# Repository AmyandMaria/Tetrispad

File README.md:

# TETRISPAD

This is a 4 key macropad with an OLED and a knob that I want to use for Tetris on TETR.IO. I play Tetris a lot on my computer, but I wanted a macropad to possibly improve playing performance. 

## CAD MODEL

## PCB

## SCHEMATIC

## FIRMWARE
I used KMK.

## BILL OF MATERIALS
- 4x Cherry MX Switches
- 4x Keycaps
- 4x M3x5x4 Heatset Inserts
- 4x M3x16mm SHCS Bolts
- 1x 0.91" 128x32 OLED Display
- 1x EC11 Rotary Encoder
- 1x XIAO RP2040
- 1x Case (3 printed parts)

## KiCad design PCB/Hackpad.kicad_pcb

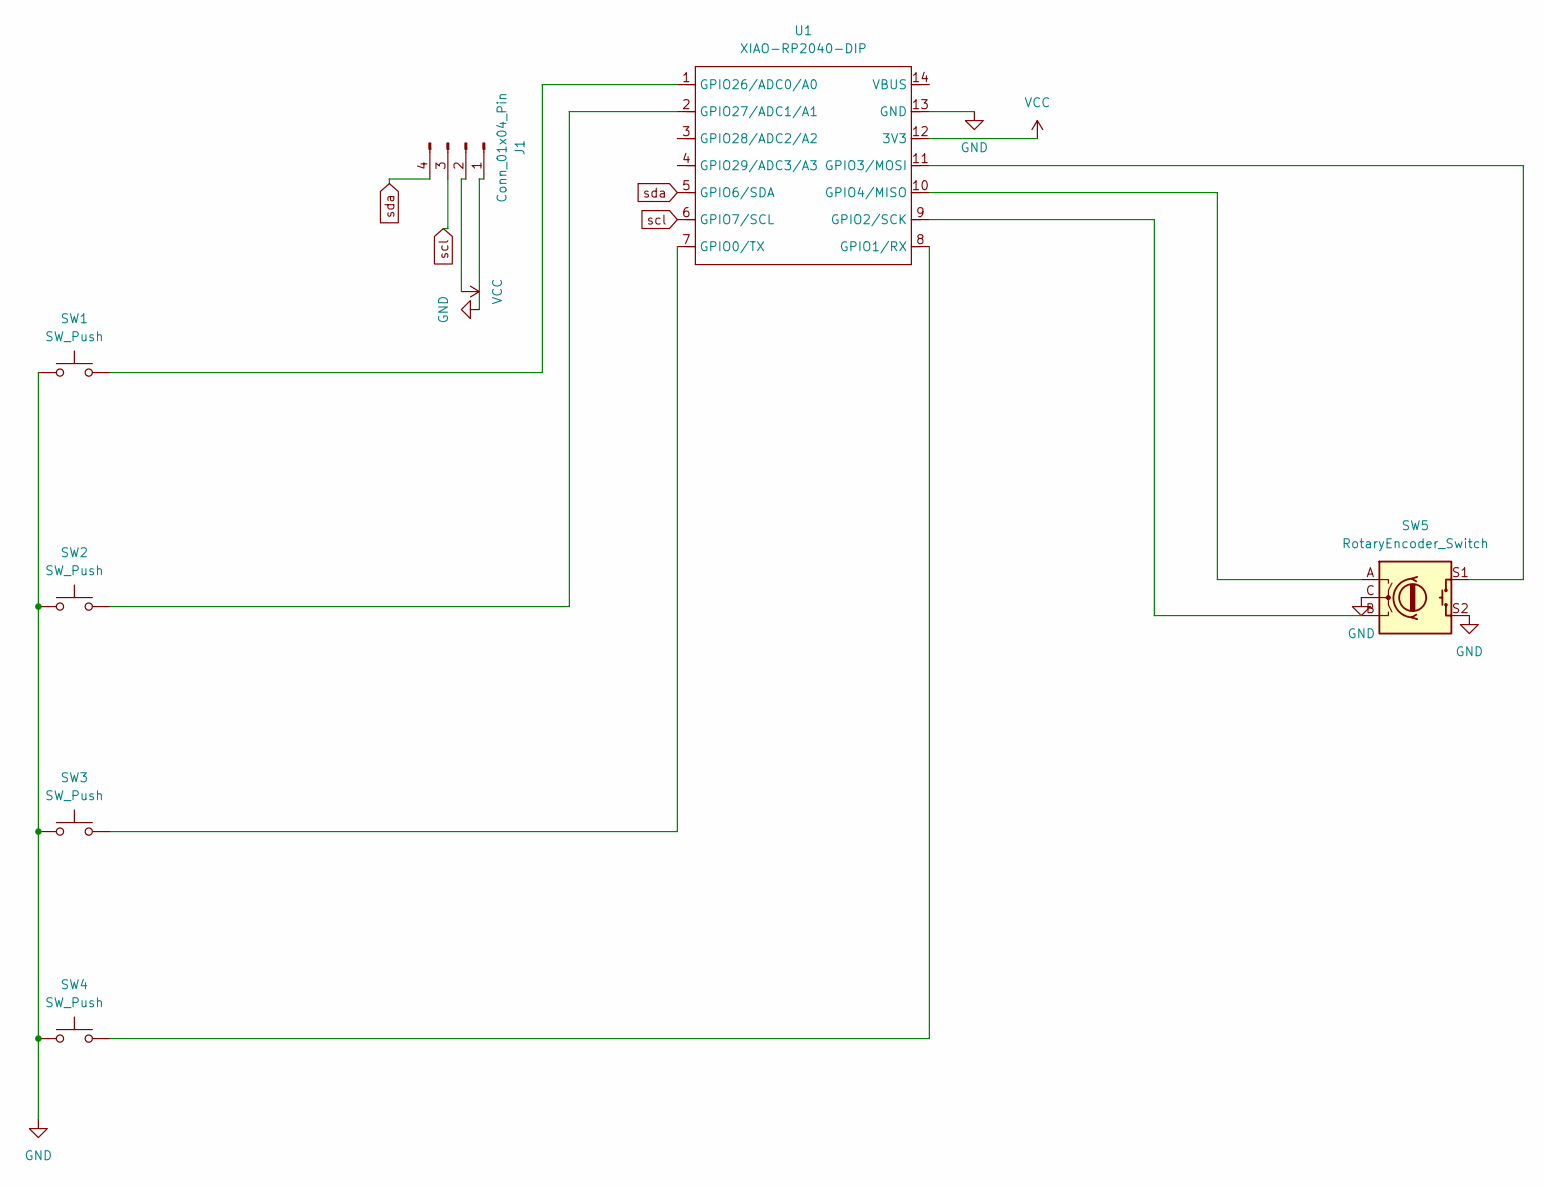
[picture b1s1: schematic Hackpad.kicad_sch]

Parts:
J1: Conn_01x04_Pin; SSD1306-0.91-OLED-4pin-128x32
SW1, SW2, SW3, SW4: SW_Push; SW_Cherry_MX_1.00u_PCB
SW5: RotaryEncoder_Switch; RotaryEncoder_Alps_EC11E-Switch_Vertical_H20mm
U1: XIAO-RP2040-DIP

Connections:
GND: J1.1, SW1.1, SW2.1, SW3.1, SW4.1, SW5.C, SW5.S2, U1.13 (GND)
unnamed: SW3.2, U1.7 (GPIO0/TX)
unnamed: SW4.2, U1.8 (GPIO1/RX)
unnamed: SW5.B, U1.9 (GPIO2/SCK)
unnamed: SW5.S1, U1.11 (GPIO3/MOSI)
unnamed: SW5.A, U1.10 (GPIO4/MISO)
unnamed: SW1.2, U1.1 (GPIO26/ADC0/A0)
unnamed: SW2.2, U1.2 (GPIO27/ADC1/A1)
VCC: J1.2, U1.12 (3V3)
scl: J1.3, U1.6 (GPIO7/SCL)
sda: J1.4, U1.5 (GPIO6/SDA)

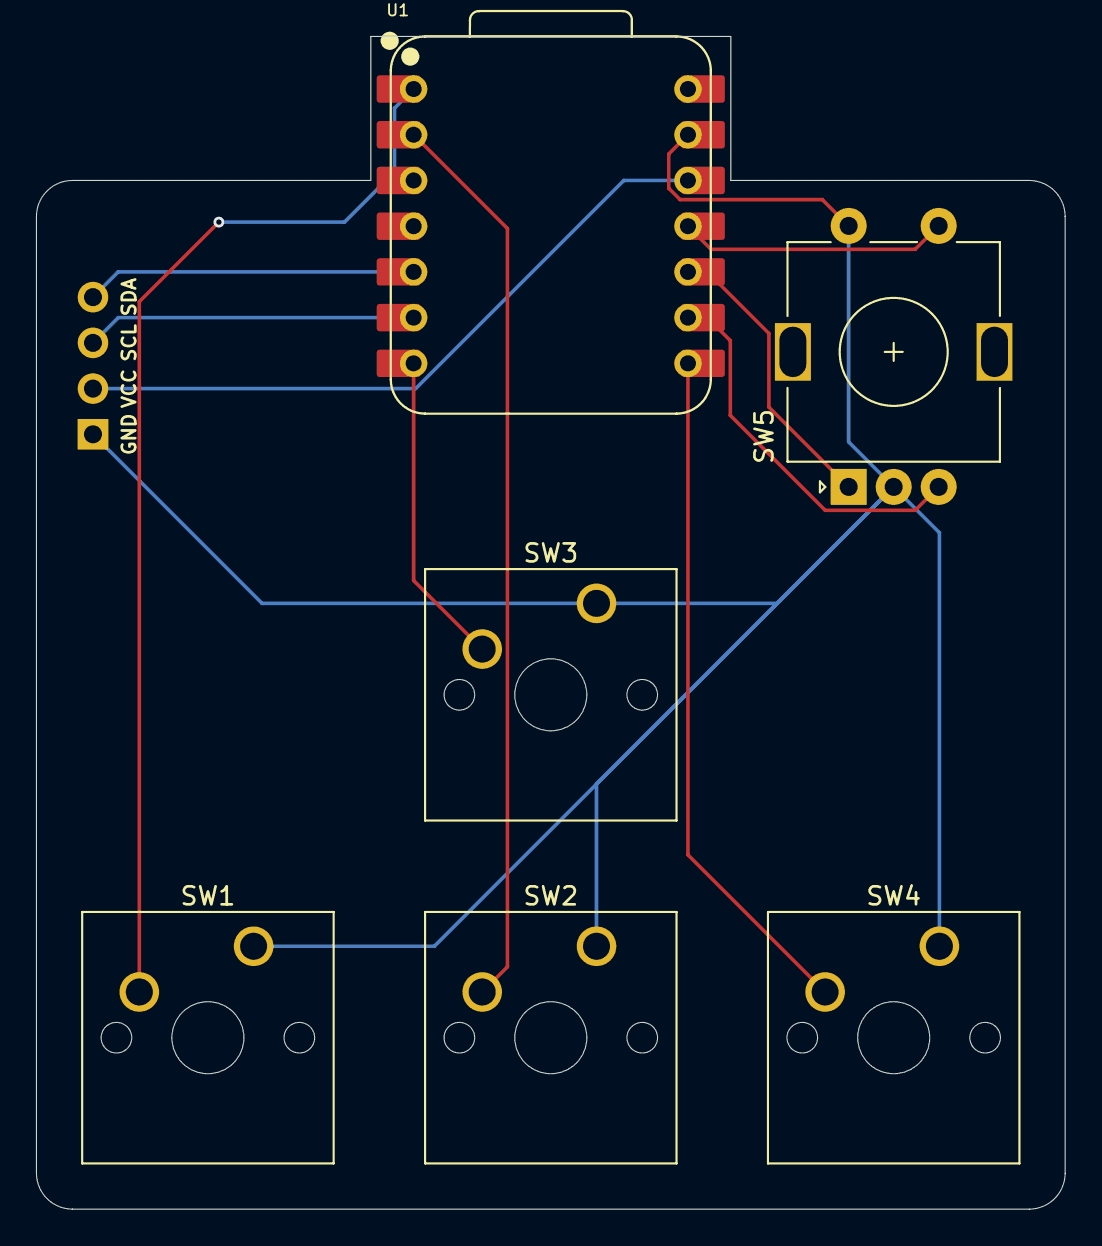
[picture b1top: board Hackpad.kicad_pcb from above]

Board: 2 copper layers, 57.2 x 65.2 mm, 7 parts (0 on the bottom side), 11 nets.

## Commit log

2025-07-08 Create d
2025-07-08 Create whateveragain
2025-07-08 Create whateveragainagain
2025-07-08 Create whateveragainagainagain
